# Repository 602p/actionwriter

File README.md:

# actionwriter
Drivers and utilities for my IBM ActionWriter keyboard

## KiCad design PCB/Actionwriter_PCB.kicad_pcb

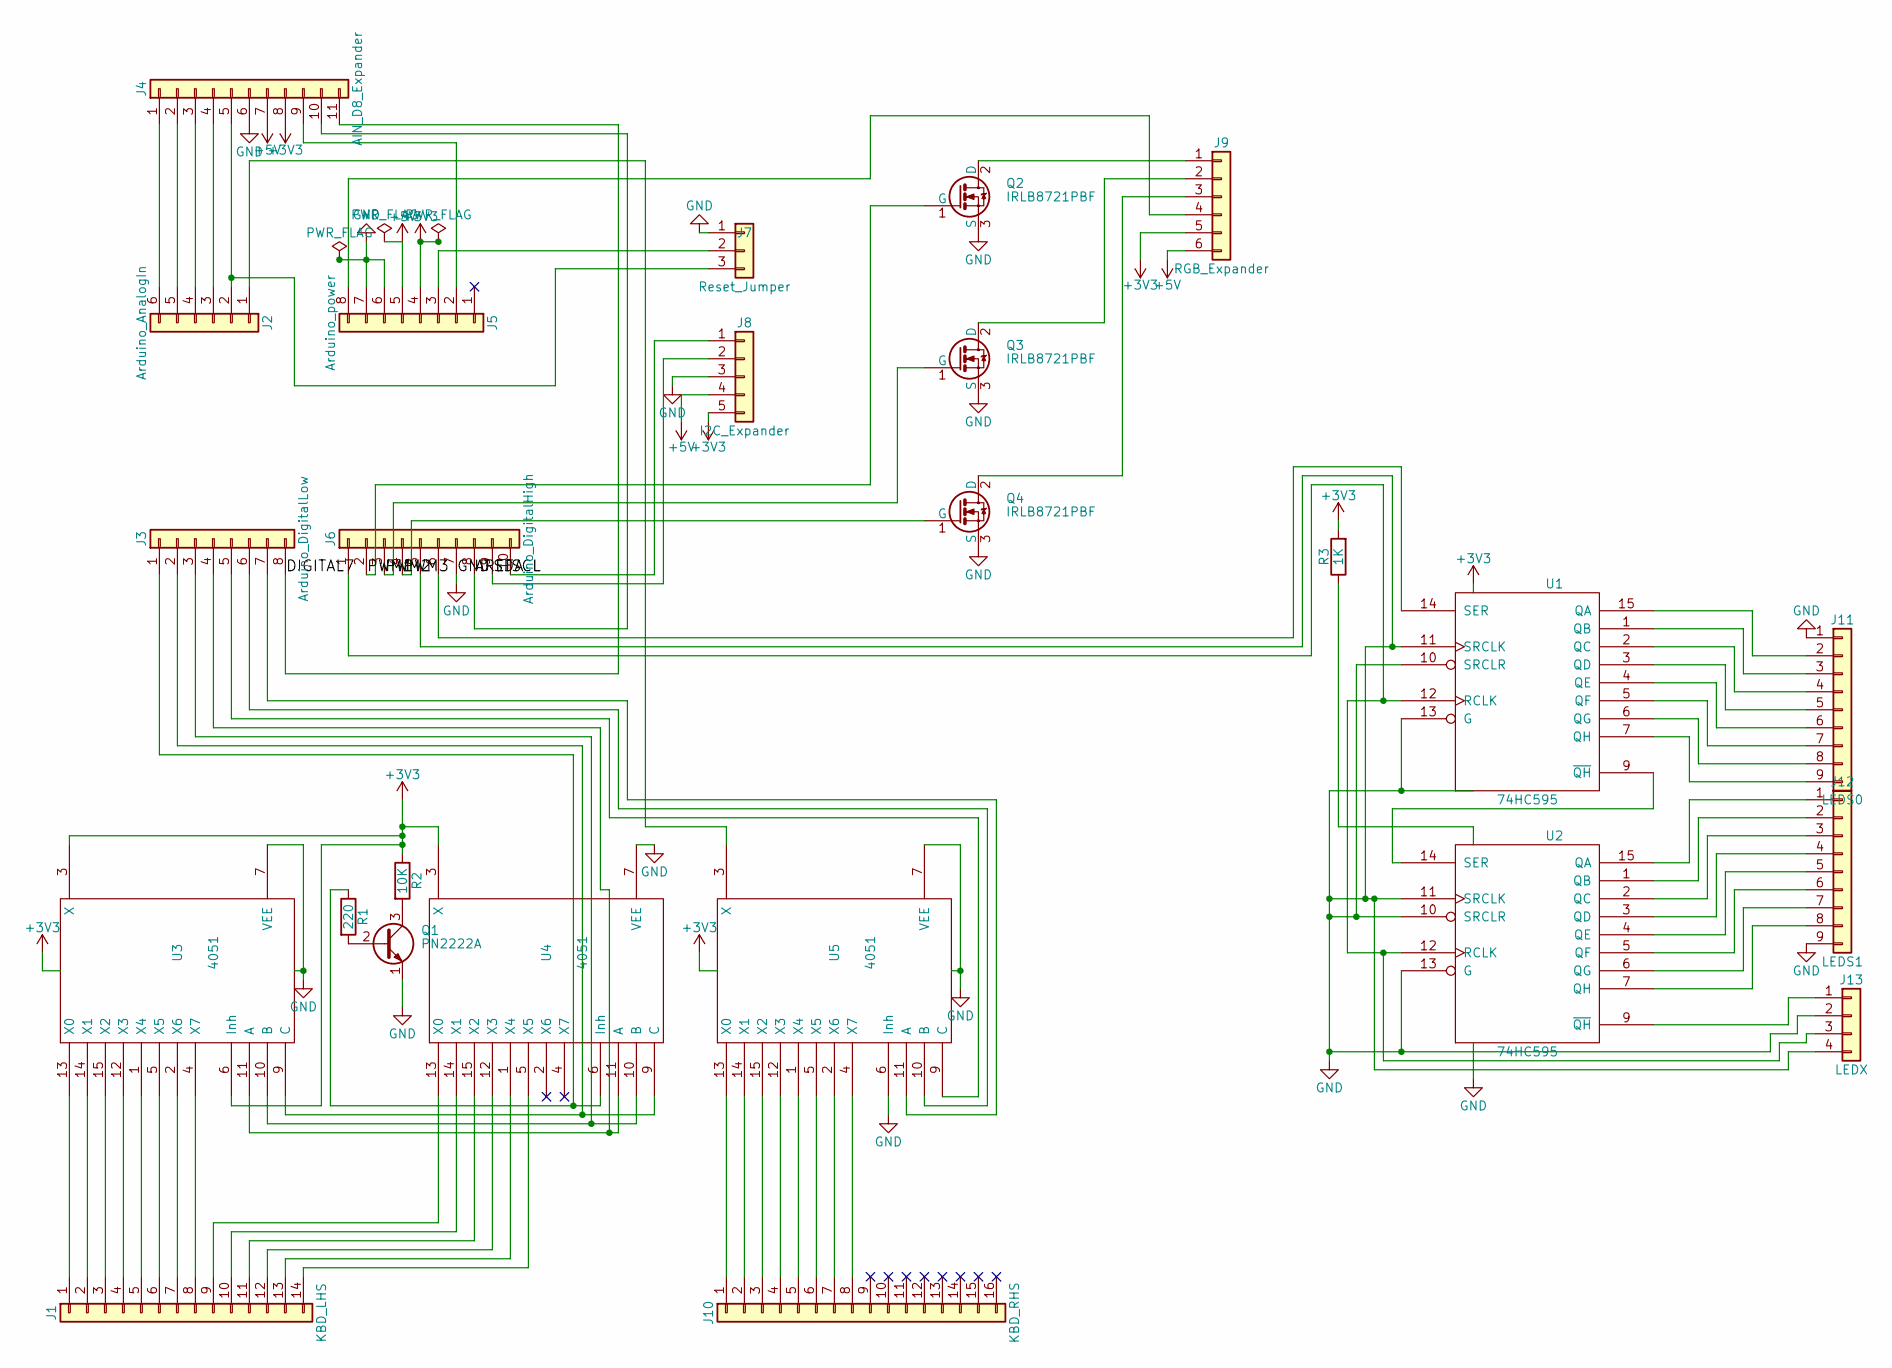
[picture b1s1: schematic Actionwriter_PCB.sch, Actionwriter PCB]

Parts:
J1: KBD_LHS; Pin_Header_Straight_1x14_Pitch2.54mm
J2: Arduino_AnalogIn; Pin_Header_Straight_1x06_Pitch2.54mm
J3: Arduino_DigitalLow; Pin_Header_Straight_1x08_Pitch2.54mm
J4: AIN_D8_Expander; Pin_Header_Straight_1x11_Pitch2.54mm
J5: Arduino_power; Pin_Header_Straight_1x08_Pitch2.54mm
J6: Arduino_DigitalHigh; Pin_Header_Straight_1x10_Pitch2.54mm
J7: Reset_Jumper; Pin_Header_Straight_1x03_Pitch2.54mm
J8: I2C_Expander; Pin_Header_Straight_1x05_Pitch2.54mm
J9: RGB_Expander; Pin_Header_Straight_1x06_Pitch2.54mm
J10: KBD_RHS; Pin_Header_Straight_1x14_Pitch2.54mm
J11: LEDS0; Pin_Header_Straight_1x09_Pitch2.54mm
J12: LEDS1; Pin_Header_Straight_1x09_Pitch2.54mm
J13: LEDX; Pin_Header_Straight_1x04_Pitch1.27mm_SMD_Pin1Right
Q1: PN2222A; TO-92_Molded_Narrow
Q2, Q3, Q4: IRLB8721PBF; TO-220-3_Vertical
R1: 220; R_1206_HandSoldering
R2: 10K; R_1206_HandSoldering
R3: 1K; R_1206_HandSoldering
U1, U2: 74HC595; DIP-16_W7.62mm
U3, U4, U5: 4051; DIP-16_W7.62mm

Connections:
+5V: J4.7, J5.5, J8.4, J9.6
/AREF: J4.10, J6.8
/DIGITAL7: J3.8, J4.11
/PWM1: J6.2, Q2.1 (G)
/PWM2: J6.3, Q3.1 (G)
/PWM3: J6.4, Q4.1 (G)
/SCL: J6.10, J8.1
/SDA: J6.9, J8.2
GND: J4.6, J5.6, J5.7, J6.5, J6.7, J7.1, J8.3, J11.1, J12.9, J13.2, J13.4, Q1.1 (E), Q2.3 (S), Q3.3 (S), Q4.3 (S), U1.8 (GND), U1.10 (SRCLR), U1.11 (SRCLK), U1.13 (G), U2.8 (GND), U2.10 (SRCLR), U2.11 (SRCLK), U2.13 (G), U3.7 (VEE), U3.8 (VSS), U4.7 (VEE), U4.8 (VSS), U5.6 (Inh), U5.7 (VEE), U5.8 (VSS)
unnamed: J1.1, U3.13 (X0)
unnamed: J1.2, U3.14 (X1)
unnamed: J1.3, U3.15 (X2)
unnamed: J1.4, U3.12 (X3)
unnamed: J1.5, U3.1 (X4)
unnamed: J1.6, U3.5 (X5)
unnamed: J1.7, U3.2 (X6)
unnamed: J1.8, U3.4 (X7)
unnamed: J1.9, U4.13 (X0)
unnamed: J1.10, U4.14 (X1)
unnamed: J1.11, U4.15 (X2)
unnamed: J1.12, U4.12 (X3)
unnamed: J1.13, U4.1 (X4)
unnamed: J1.14, U4.5 (X5)
unnamed: J2.1, U5.3 (X)
unnamed: J2.2, J4.5, J7.3
unnamed: J2.3, J4.4
unnamed: J2.4, J4.3
unnamed: J2.5, J4.2
unnamed: J2.6, J4.1
unnamed: J3.1, R1.1, U4.6 (Inh)
unnamed: J3.2, U3.9 (C), U4.9 (C)
unnamed: J3.3, U3.10 (B), U4.10 (B)
unnamed: J3.4, U3.11 (A), U4.11 (A)
unnamed: J3.5, U5.9 (C)
unnamed: J3.6, U5.10 (B)
unnamed: J3.7, U5.11 (A)
unnamed: J4.9, J5.2
unnamed: J5.3, J7.2
unnamed: J5.8, J9.4
unnamed: J6.6, U1.14 (SER)
unnamed: J9.1, Q2.2 (D)
unnamed: J9.2, Q3.2 (D)
unnamed: J9.3, Q4.2 (D)
unnamed: J10.1, U5.13 (X0)
unnamed: J10.2, U5.14 (X1)
unnamed: J10.3, U5.15 (X2)
unnamed: J10.4, U5.12 (X3)
unnamed: J10.5, U5.1 (X4)
unnamed: J10.6, U5.5 (X5)
unnamed: J10.7, U5.2 (X6)
unnamed: J10.8, U5.4 (X7)
unnamed: J11.2, U1.15 (QA)
unnamed: J11.3, U1.1 (QB)
unnamed: J11.4, U1.2 (QC)
unnamed: J11.5, U1.3 (QD)
unnamed: J11.6, U1.4 (QE)
unnamed: J11.7, U1.5 (QF)
unnamed: J11.8, U1.6 (QG)
unnamed: J11.9, U1.7 (QH)
unnamed: J12.1, U2.15 (QA)
unnamed: J12.2, U2.1 (QB)
unnamed: J12.3, U2.2 (QC)
unnamed: J12.4, U2.3 (QD)
unnamed: J12.5, U2.4 (QE)
unnamed: J12.6, U2.5 (QF)
unnamed: J12.7, U2.6 (QG)
unnamed: J12.8, U2.7 (QH)
unnamed: J13.1, U2.9 (~QH)
unnamed: J6.1, J13.3, U1.12 (RCLK), U2.12 (RCLK)
unnamed: Q1.2 (B), R1.2
unnamed: Q1.3 (C), R2.2
unnamed: U1.9 (~QH), U2.14 (SER)

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
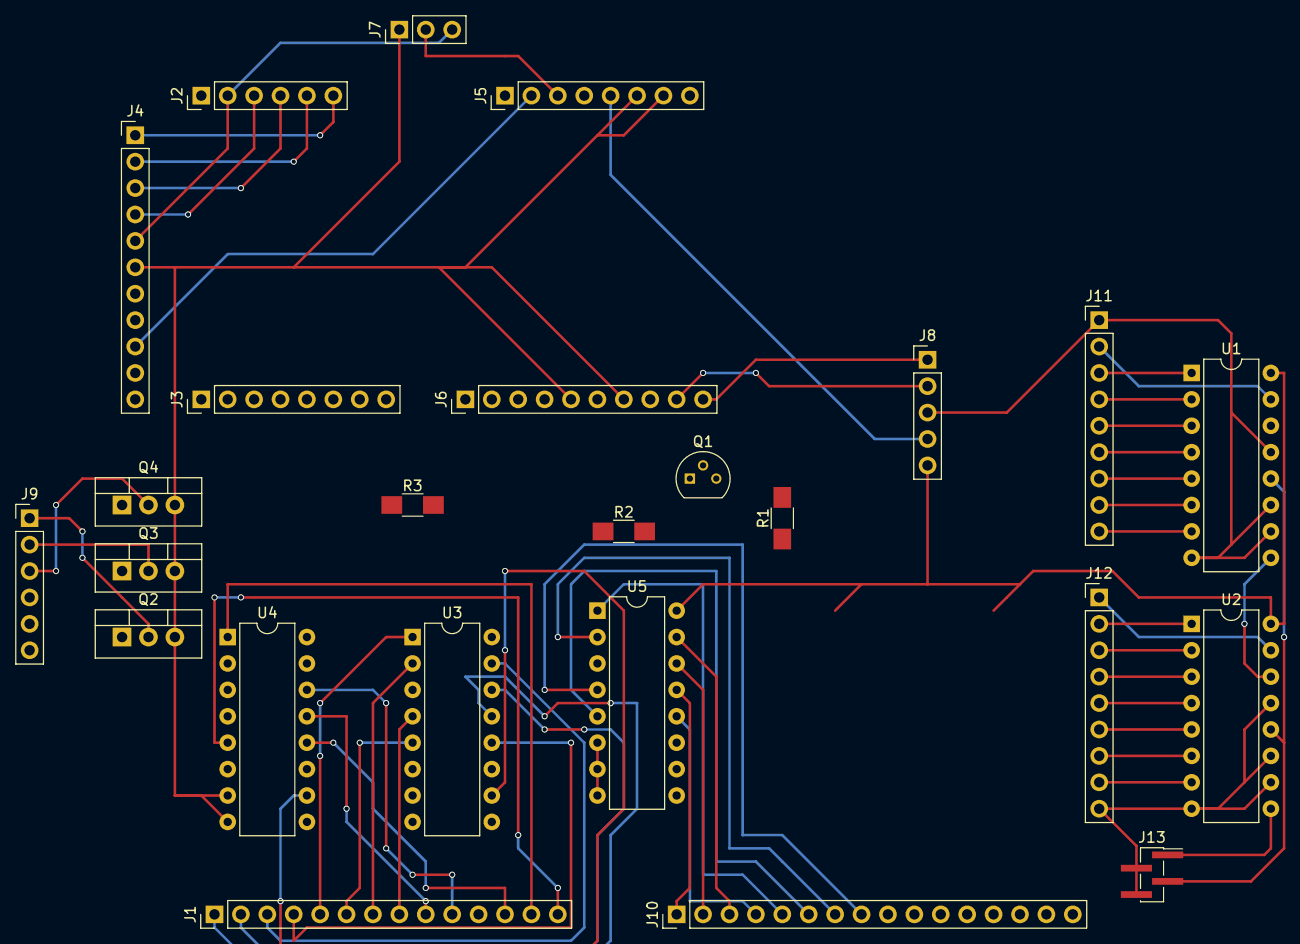
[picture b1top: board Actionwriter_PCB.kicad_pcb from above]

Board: 2 copper layers, 25 parts (0 on the bottom side), 73 nets.

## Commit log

2018-01-21 Dump stuff in here for now
2018-01-21 Misc
2018-01-21 Only TX when LEDs change, change polling
2018-01-21 Change heartbeat LED timing and add delete LMar-code
2018-01-21 Add a scancode-over-serial mode for copypastas and the like
2018-01-21 misc binding changes
2018-03-24 Some expermental PCB work, add rot13 implementation controller-side
2018-03-24 Schematic seems finished
2018-03-24 Test moving some address lines to 0 and 1 (for later use of PWM), PCB work
2018-03-25 Add dumb (non computer-side hardware requiring) mode via A2 jumper
2018-03-26 remove crap
2018-03-26 add pdf
2018-03-26 actually add PDF
2018-06-10 updated?
2018-06-11 reorg
2018-06-12 wtf why not wrk
2018-06-12 still not working:
2018-06-12 works but idk why
2018-06-12 working
2018-06-12 mask
2018-06-12 masked
2018-06-12 move to top
2018-06-12 move up
2018-06-12 Working controller!
2018-06-12 setting up for real work
2018-06-12 stash
2018-06-13 aside from a mystery issue, fine
2018-06-13 diodes!
2018-06-14 move pcb
2018-06-15 F-keys
2018-06-15 better meta shift solution, fix keys getting stuck when meta-shifting, fix mapping for equals key
